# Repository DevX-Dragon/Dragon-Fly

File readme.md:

# Your in the wrong brach. :)

This branch is to host the prodcut display website live on https://devx-dragon.github.io/Dragon-Fly/
Go to the main brach :)

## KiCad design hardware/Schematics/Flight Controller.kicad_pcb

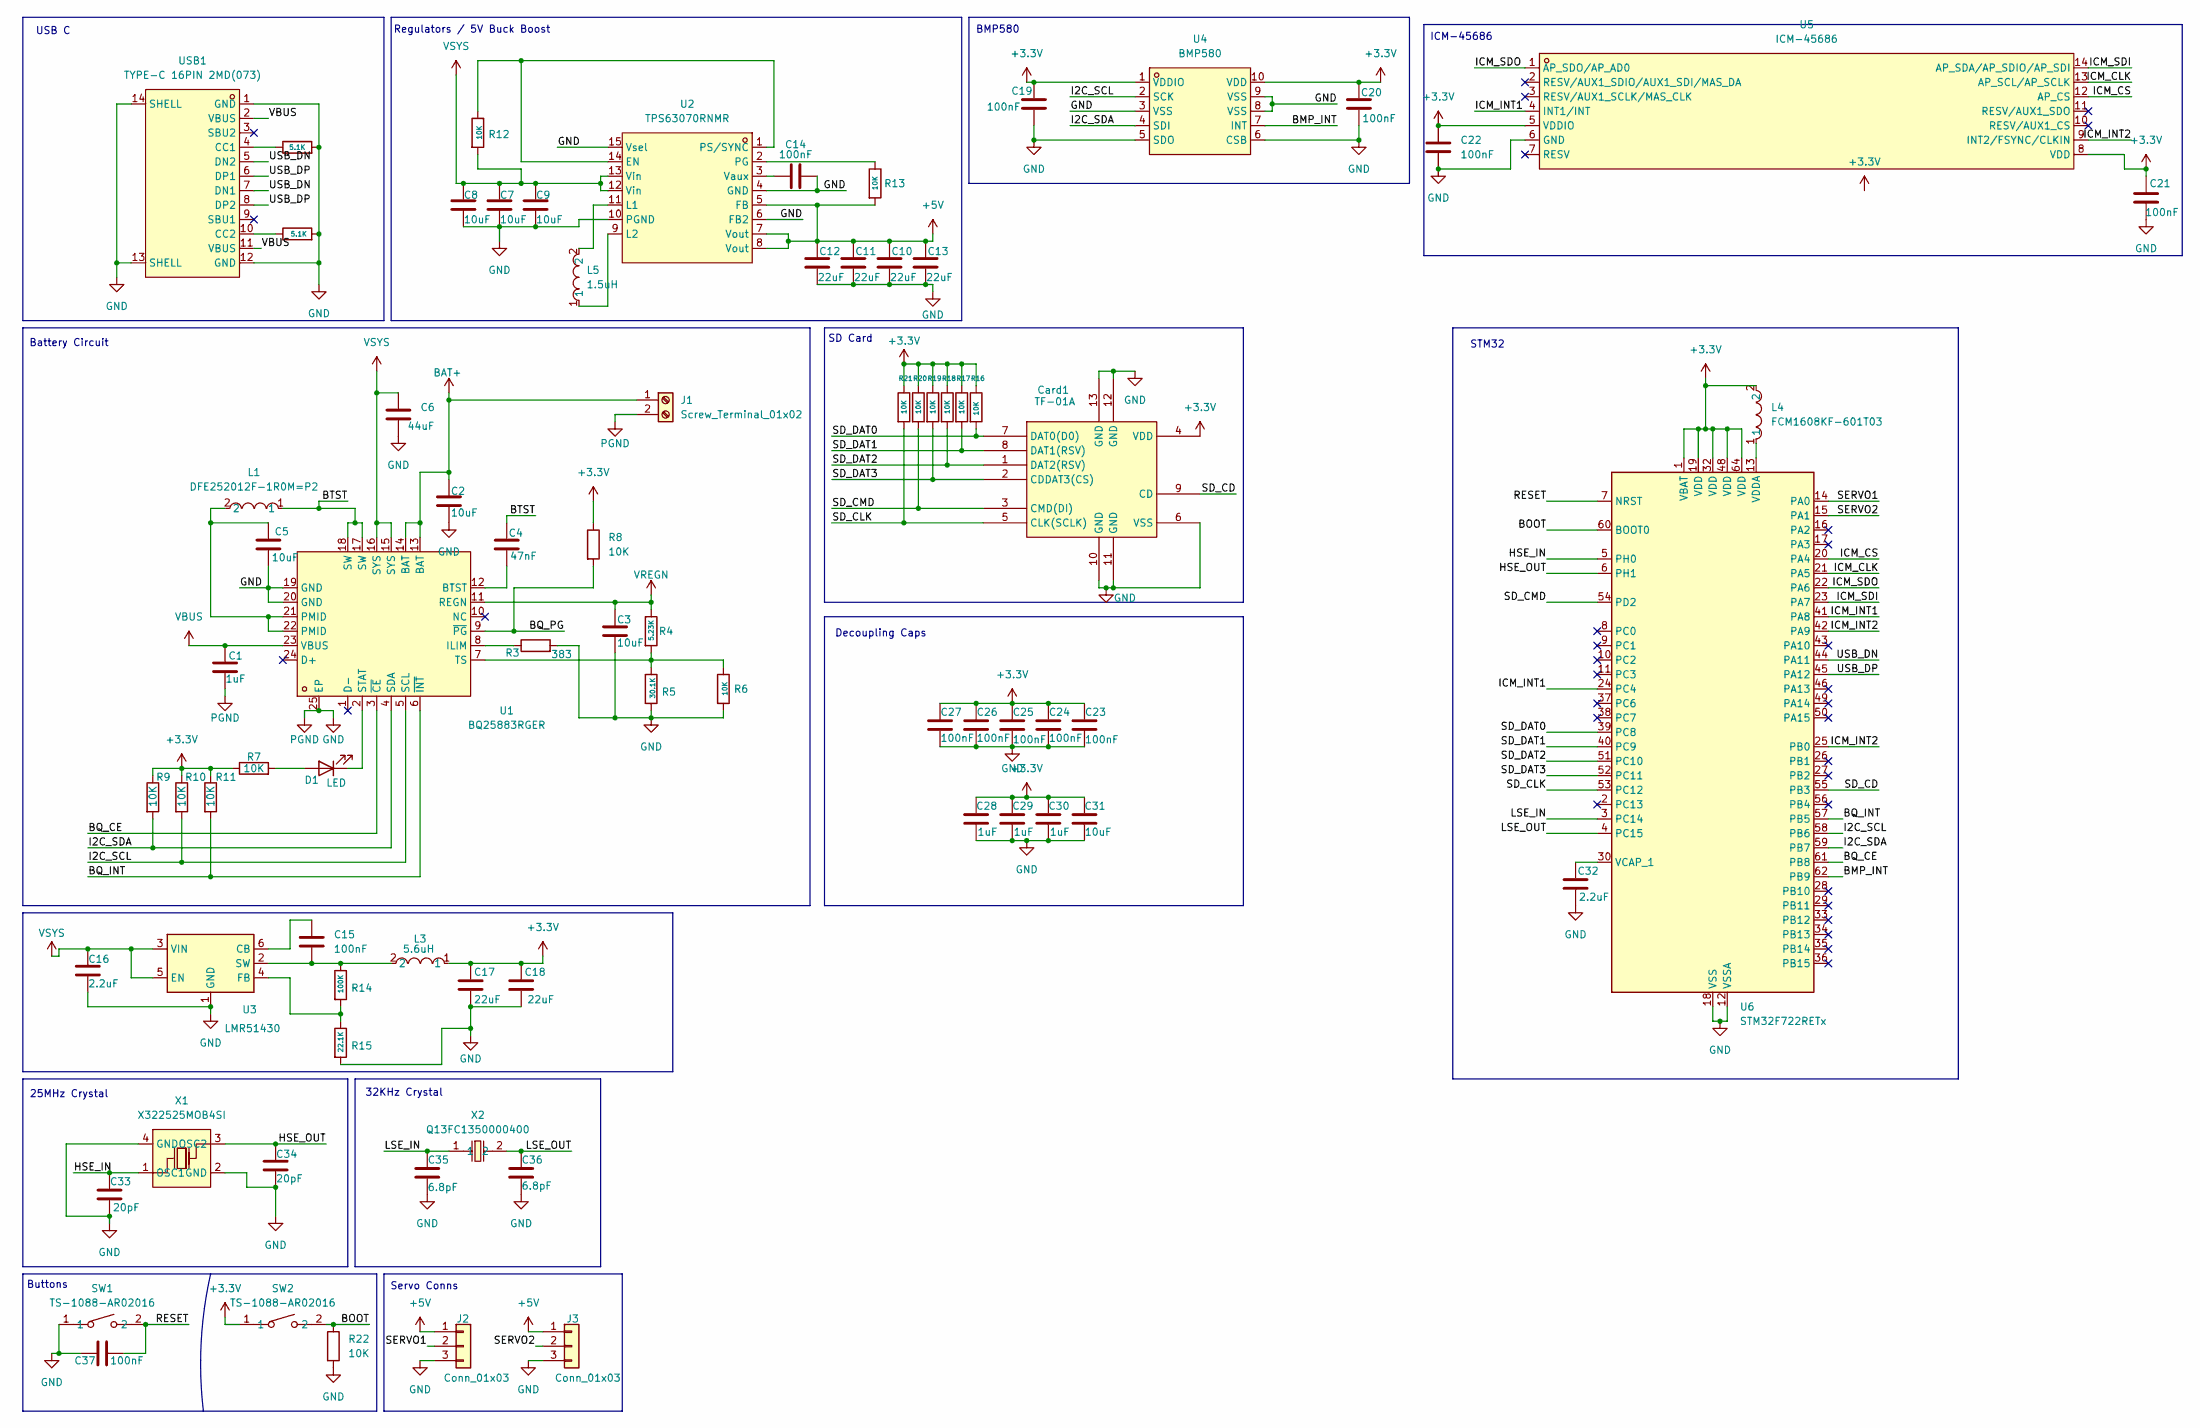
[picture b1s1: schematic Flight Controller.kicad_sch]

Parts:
C1, C28, C29, C30: 1uF; C_0603_1608Metric
C2, C3, C5, C7, C8, C9, C31: 10uF; C_0603_1608Metric
C4: 47nF; C_0603_1608Metric
C6: 44uF; C_0603_1608Metric
C10, C11, C12, C13, C17, C18: 22uF; C_0603_1608Metric
C14, C15: 100nF; C_0603_1608Metric
C16, C32: 2.2uF; C_0603_1608Metric
C19, C20, C21, C22, C23, C24, C25, C26, C27, C37: 100nF; C_0402_1005Metric
C33, C34: 20pF; C_0402_1005Metric
C35, C36: 6.8pF; C_0402_1005Metric
Card1: TF-01A; TF-SMD_TF-01A; LCSC Part C91145
D1: LED; LED_0402_1005Metric
J1: Screw_Terminal_01x02; TerminalBlock_Xinya_XY308-2.54-2P_1x02_P2.54mm_Horizontal
J2, J3: Conn_01x03; PinHeader_2x03_P2.54mm_Vertical
L1: DFE252012F-1R0M=P2; LED_0402_1005Metric; LCSC Part C435392
L3: 5.6uH; L2520; LCSC Part C435392
L4: FCM1608KF-601T03; L0603; LCSC Part C141723
L5: 1.5uH; IND-SMD_L3.0-W3.0; LCSC Part C18236327
R1, R2: 5.1K; R_0201_0603Metric
R3: 383; R_0201_0603Metric
R4: 5.23K; R_0201_0603Metric
R5: 30.1K; R_0201_0603Metric
R6, R7, R8, R9, R10, R11, R12, R13, R16, R17, R18, R19, R20, R21, R22: 10K; R_0201_0603Metric
R14: 100K; R_0402_1005Metric
R15: 22.1K; R_0201_0603Metric
SW1, SW2: TS-1088-AR02016; SW-SMD_L3.9-W3.0-P4.45; LCSC Part C720477
U1: BQ25883RGER; VFQFPN-24_L4.0-W4.0-P0.50-BL-EP2.8; LCSC Part C544362
U2: TPS63070RNMR; VQFN-HR-15_L3.0-W2.5-P0.50-BL_TPS63070RNMR; LCSC Part C109322
U3: LMR51430; SOT-23-6
U4: BMP580; LGA-10_L2.0-W2.0-P0.50-TL_BMP580; LCSC Part C22391138
U5: ICM-45686; LGA-14_L3.0-W2.5-P0.50-TL; LCSC Part C22459454
U6: STM32F722RETx; LQFP-64_10x10mm_P0.5mm
USB1: TYPE-C 16PIN 2MD(073); USB-C-SMD_TYPE-C-6PIN-2MD-073; LCSC Part C2765186
X1: X322525MOB4SI; CRYSTAL-SMD_4P-L3.2-W2.5-BL; LCSC Part C9006
X2: Q13FC1350000400; FC-135R_L3.2-W1.5; LCSC Part C32346

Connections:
+3.3V: C17.1, C18.1, C19.1, C20.1, C21.1, C22.1, C23.1, C24.1, C25.1, C26.1, C27.1, C28.1, C29.1, C30.1, C31.1, Card1.4 (VDD), L3.1, L4.2, R7.1, R8.1, R9.1, R10.1, R11.1, R16.1, R17.1, R18.1, R19.1, R20.1, R21.1, SW2.1, U4.1 (VDDIO), U4.10 (VDD), U5.5 (VDDIO), U5.8 (VDD), U6.1 (VBAT), U6.19 (VDD), U6.32 (VDD), U6.48 (VDD), U6.64 (VDD)
+5V: C10.1, C11.1, C12.1, C13.1, J2.1, J3.1, R13.2, U2.5 (FB), U2.7 (Vout), U2.8 (Vout)
/BMP_INT: U4.7 (INT), U6.62 (PB9)
/BOOT: R22.1, SW2.2, U6.60 (BOOT0)
/BQ_CE: U1.3 (~CE), U6.61 (PB8)
/BQ_INT: R11.2, U1.6 (~INT), U6.57 (PB5)
/BQ_PG: R8.2, U1.9 (~PG)
/BTST: C4.1, L1.1, U1.17 (SW), U1.18 (SW)
/HSE_IN: C33.1, U6.5 (PH0), X1.1 (OSC1)
/HSE_OUT: C34.1, U6.6 (PH1), X1.3 (OSC2)
/I2C_SCL: R10.2, U1.5 (SCL), U4.2 (SCK), U6.58 (PB6)
/I2C_SDA: R9.2, U1.4 (SDA), U4.4 (SDI), U6.59 (PB7)
/ICM_CLK: U5.13 (AP_SCL/AP_SCLK), U6.21 (PA5)
/ICM_CS: U5.12 (AP_CS), U6.20 (PA4)
/ICM_INT1: U5.4 (INT1/INT), U6.24 (PC4), U6.41 (PA8)
/ICM_INT2: U5.9 (INT2/FSYNC/CLKIN), U6.25 (PB0), U6.42 (PA9)
/ICM_SDI: U5.14 (AP_SDA/AP_SDIO/AP_SDI), U6.23 (PA7)
/ICM_SDO: U5.1 (AP_SDO/AP_AD0), U6.22 (PA6)
/LSE_IN: C35.1, U6.3 (PC14), X2.1
/LSE_OUT: C36.1, U6.4 (PC15), X2.2
/RESET: C37.2, SW1.2, U6.7 (NRST)
/SD_CD: Card1.9 (CD), U6.55 (PB3)
/SD_CLK: Card1.5 (CLK(SCLK)), R21.2, U6.53 (PC12)
/SD_CMD: Card1.3 (CMD(DI)), R20.2, U6.54 (PD2)
/SD_DAT0: Card1.7 (DAT0(D0)), R16.2, U6.39 (PC8)
/SD_DAT1: Card1.8 (DAT1(RSV)), R17.2, U6.40 (PC9)
/SD_DAT2: Card1.1 (DAT2(RSV)), R18.2, U6.51 (PC10)
/SD_DAT3: Card1.2 (CDDAT3(CS)), R19.2, U6.52 (PC11)
/SERVO1: J2.2, U6.14 (PA0)
/SERVO2: J3.2, U6.15 (PA1)
/USB_DN: U6.44 (PA11), USB1.5 (DN2), USB1.7 (DN1); also elsewhere on the board
/USB_DP: U6.45 (PA12), USB1.6 (DP1), USB1.8 (DP2); also elsewhere on the board
BAT+: C2.1, J1.1, U1.13 (BAT), U1.14 (BAT)
GND: C1.2, C2.2, C3.2, C5.2, C6.2, C7.2, C8.2, C9.2, C10.2, C11.2, C12.2, C13.2, C14.2, C16.2, C17.2, C18.2, C19.2, C20.2, C21.2, C22.2, C23.2, C24.2, C25.2, C26.2, C27.2, C28.2, C29.2, C30.2, C31.2, C32.2, C33.2, C34.2, C35.2, C36.2, C37.1, Card1.6 (VSS), Card1.10 (GND), Card1.11 (GND), Card1.12 (GND), Card1.13 (GND), J1.2, J2.3, J3.3, R1.2, R2.2, R3.2, R5.2, R6.2, R15.2, R22.2, SW1.1, U1.19 (GND), U1.20 (GND), U1.25 (EP), U2.4 (GND), U2.6 (FB2), U2.10 (PGND), U2.15 (Vsel), U3.1 (GND), U4.3 (VSS), U4.5 (SDO), U4.6 (CSB), U4.8 (VSS), U4.9 (VSS), U5.6 (GND), U6.12 (VSSA), U6.18 (VSS), U6.31 (VSS), U6.47 (VSS), U6.63 (VSS), USB1.1 (GND), USB1.12 (GND), USB1.13 (SHELL), USB1.14 (SHELL), X1.2 (GND), X1.4 (GND); also elsewhere on the board
unnamed: C5.1, L1.2, U1.21 (PMID), U1.22 (PMID)
unnamed: D1.2 (A), R7.2
unnamed: D1.1 (K), U1.2 (STAT)
unnamed: C4.2, U1.12 (BTST)
unnamed: R3.1, U1.8 (ILIM)
unnamed: R4.2, R5.1, R6.1, U1.7 (TS)
unnamed: R12.1, U2.1 (PS/SYNC), U2.14 (EN)
unnamed: L5.2, U2.11 (L1)
unnamed: L5.1, U2.9 (L2)
unnamed: R13.1, U2.2 (PG)
unnamed: C14.1, U2.3 (Vaux)
unnamed: C15.1, U3.6 (CB)
unnamed: R14.2, R15.1, U3.4 (FB)
unnamed: C15.2, L3.2, R14.1, U3.2 (SW)
unnamed: C32.1, U6.30 (VCAP_1)
unnamed: L4.1, U6.13 (VDDA)
unnamed 50: R1.1, USB1.4 (CC1); also elsewhere on the board
unnamed 51: R2.1, USB1.10 (CC2); also elsewhere on the board
unnamed: USB1.2 (VBUS), USB1.11 (VBUS)
VBUS: C1.1, U1.23 (VBUS); also elsewhere on the board
VREGN: C3.1, R4.1, U1.11 (REGN)
VSYS: C6.1, C7.1, C8.1, C9.1, C16.1, R12.2, U1.15 (SYS), U1.16 (SYS), U2.12 (Vin), U2.13 (Vin), U3.3 (VIN), U3.5 (EN)

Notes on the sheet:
Decoupling Caps
32KHz Crystal
ICM-45686
Battery Circuit
SD Card
BMP580
Regulators / 5V Buck Boost
USB C
Buttons
25MHz Crystal
Servo Conns
STM32

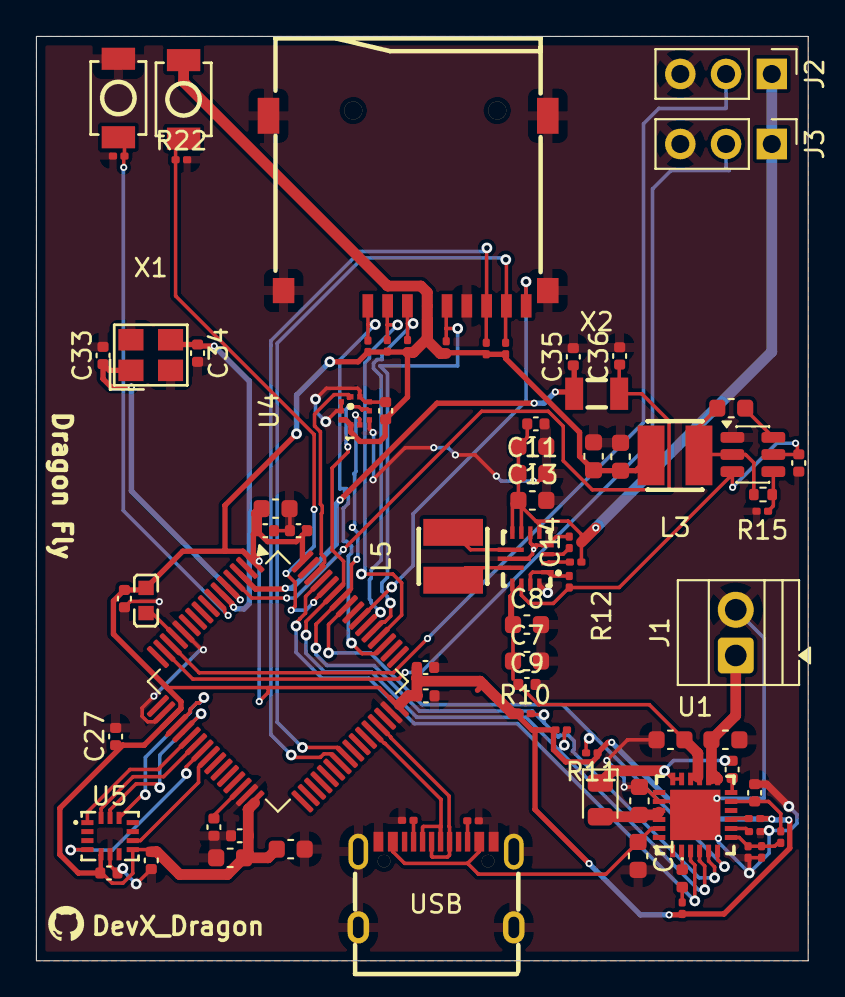
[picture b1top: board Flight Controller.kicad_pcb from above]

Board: 2 copper layers, 42.9 x 51.4 mm, 79 parts (0 on the bottom side), 55 nets.

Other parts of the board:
USB: TYPE-C 16PIN 2MD(073); USB-C-SMD_TYPE-C-6PIN-2MD-073

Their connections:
/USB_DN: USB.5 (DN2), USB.7 (DN1); also elsewhere on the board
/USB_DP: USB.6 (DP1), USB.8 (DP2); also elsewhere on the board
GND: USB.1 (GND), USB.12 (GND), USB.13 (SHELL), USB.14 (SHELL); also elsewhere on the board
unnamed 50: USB.4 (CC1); also elsewhere on the board
unnamed 51: USB.10 (CC2); also elsewhere on the board
VBUS: USB.2 (VBUS), USB.11 (VBUS); also elsewhere on the board

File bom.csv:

Designator,Footprint,Quantity,Value,LCSC Part #
"C1, C29, C30",0603,3,1uF,
"C10, C11, C13, C17, C18",0603,5,22uF,
C12,0402,1,22uF,
"C14, C37",0201,2,100nF,
C15,0603,1,100nF,
"C16, C32",0402,2,2.2uF,
"C19, C20, C21, C22, C23, C24, C25, C26, C27",0402,9,100nF,
"C2, C31, C5, C7, C8",0603,5,10uF,
C28,0402,1,1uF,
"C3, C9",0402,2,10uF,
"C33, C34",0402,2,20pF,
"C35, C36",0402,2,6.8pF,
C4,0402,1,47nF,
C6,0603,1,44uF,
CARD1,TF-SMD_TF-01A,1,TF-01A,C91145
D1,0402,1,LED,
J1,TerminalBlock_Xinya_XY308-2.54-2P_1x02_P2.54mm_Horizontal,1,Screw_Terminal_01x02,
"J2, J3",PinHeader_1x03_P2.54mm_Vertical,2,Conn_01x03,
L1,0805,1,DFE252012F-1R0M=P2,C435392
L3,IND-SMD_L3.0-W3.0,1,5.6uH,C435392
L4,L0603,1,FCM1608KF-601T03,C141723
L5,IND-SMD_L3.0-W3.0,1,1.5uH,C18236327
"R1, R2",0201,2,5.1K,
"R10, R11, R12, R13, R16, R17, R18, R19, R20, R21, R22, R6, R7, R8, R9",0201,15,10K,
R14,0402,1,100K,
R15,0201,1,22.1K,
R3,0201,1,383,
R4,0201,1,5.23K,
R5,0201,1,30.1K,
"SW1, SW2",SW-SMD_L3.9-W3.0-P4.45,2,TS-1088-AR02016,C720477
U1,VFQFPN-24_L4.0-W4.0-P0.50-BL-EP2.8,1,BQ25883RGER,C544362
U2,VQFN-HR-15_L3.0-W2.5-P0.50-BL_TPS63070RNMR,1,TPS63070RNMR,C109322
U3,SOT-23-6,1,LMR51430,
U4,LGA-10_L2.0-W2.0-P0.50-TL_BMP580,1,BMP580,C22391138
U5,LGA-14_L3.0-W2.5-P0.50-TL,1,ICM-45686,C22459454
U6,LQFP-64_10x10mm_P0.5mm,1,STM32F722RETx,
USB,USB-C-SMD_TYPE-C-6PIN-2MD-073,1,TYPE-C 16PIN 2MD(073),C2765186
X1,CRYSTAL-SMD_4P-L3.2-W2.5-BL,1,X322525MOB4SI,C9006
X2,FC-135R_L3.2-W1.5,1,Q13FC1350000400,C32346

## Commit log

2026-01-11 Add files via upload
    the .s file is the Standard CMSIS startup script for STM32F722RETx. Initializes Vector Table and calls SystemInit before jumping to main.
